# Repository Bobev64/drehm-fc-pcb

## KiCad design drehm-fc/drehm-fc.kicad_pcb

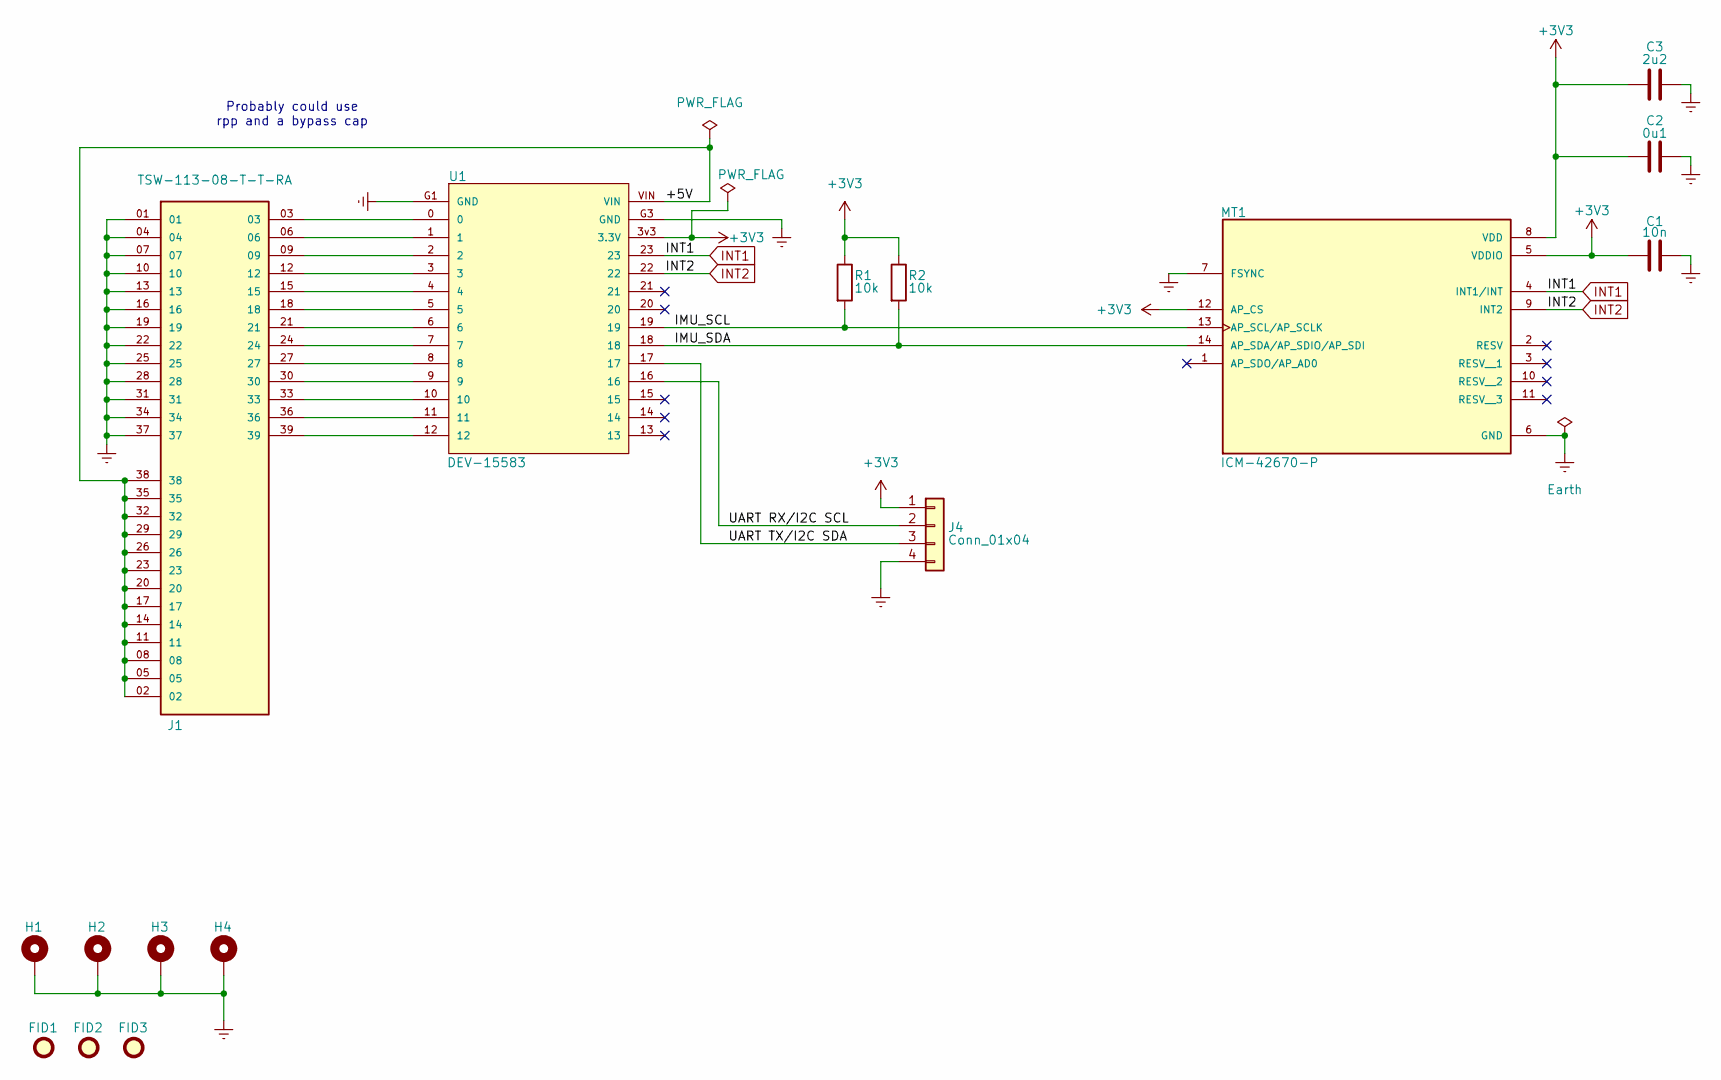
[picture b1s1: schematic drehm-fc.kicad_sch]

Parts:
C1: 10n; C_0402_1005Metric; Manufacturer P/N GRM033R61C103KA12D
C2: 0u1; C_0402_1005Metric; Manufacturer P/N GRM033Z71A104KE14D
C3: 2u2; C_0402_1005Metric; Manufacturer P/N GRM033R60J225ME47D
FID1, FID2, FID3: Fiducial; Fiducial_1mm_Mask2mm
H1, H2, H3, H4: Mounting Hole; MountingHole_3.2mm_M3_DIN965_Pad
J1: TSW-113-08-T-T-RA; SAMTEC_TSW-113-08-T-T-RA; PARTREV R
J4: Conn_01x04; PinHeader_1x04_P2.54mm_Vertical
MT1: ICM-42670-P; XDCR_ICM-42670-P; PARTREV 1.1
R1, R2: 10k; R_0402_1005Metric; Manufacturer P/N ERA1AEB103C
U1: DEV-15583; MODULE_DEV-15583

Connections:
+3V3: C1.1, C2.1, C3.1, J4.1, MT1.5 (VDDIO), MT1.8 (VDD), MT1.12 (AP_CS), R1.1, R2.1, U1.3v3 (3.3V)
/+5V: J1.02, J1.05, J1.08, J1.11, J1.14, J1.17, J1.20, J1.23, J1.26, J1.29, J1.32, J1.35, J1.38, U1.VIN
/IMU_SCL: MT1.13 (AP_SCL/AP_SCLK), R1.2, U1.19
/IMU_SDA: MT1.14 (AP_SDA/AP_SDIO/AP_SDI), R2.2, U1.18
/UART RX/I2C SCL: J4.2, U1.16
/UART TX/I2C SDA: J4.3, U1.17
Earth: C1.2, C2.2, C3.2, H1.1, H2.1, H3.1, H4.1, J1.01, J1.04, J1.07, J1.10, J1.13, J1.16, J1.19, J1.22, J1.25, J1.28, J1.31, J1.34, J1.37, J4.4, MT1.6 (GND), MT1.7 (FSYNC), U1.G1 (GND), U1.G3 (GND)
INT1: MT1.4 (INT1/INT), U1.23
INT2: MT1.9 (INT2), U1.22
unnamed: J1.03, U1.0
unnamed: J1.06, U1.1
unnamed: J1.09, U1.2
unnamed: J1.12, U1.3
unnamed: J1.15, U1.4
unnamed: J1.18, U1.5
unnamed: J1.21, U1.6
unnamed: J1.24, U1.7
unnamed: J1.27, U1.8
unnamed: J1.30, U1.9
unnamed: J1.33, U1.10
unnamed: J1.36, U1.11
unnamed: J1.39, U1.12

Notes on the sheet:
Probably could use rpp and a bypass cap

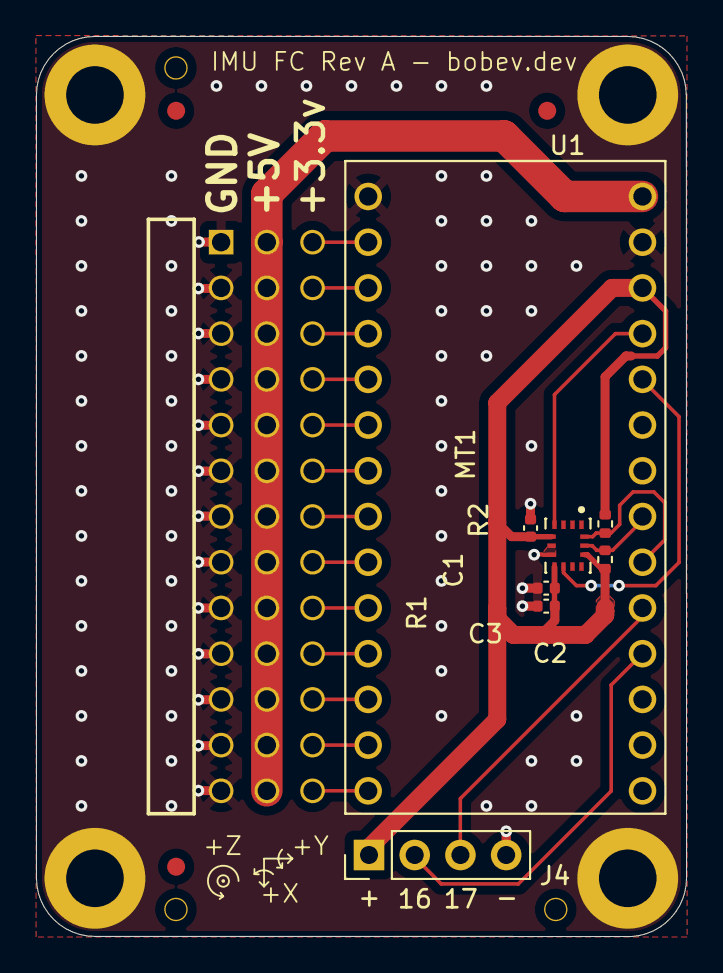
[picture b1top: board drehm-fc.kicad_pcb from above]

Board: 2 copper layers, 36.1 x 50.0 mm, 16 parts (0 on the bottom side), 22 nets.

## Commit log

2024-08-05 Design uses ICM-42670, rpp is wip
2024-08-14 Schematic V1, PCB WIP
2024-08-14 design rules set, teensy footprint modified
2024-08-16 IMU Routing finished, board outline done
2024-08-16 Routing mostly done, finishing touches WIP
2024-08-19 name and rev on silkscreen
2024-08-19 Manufacturability changes, silkscreen update
2024-08-20 0402 conversion, added holes for PCBA
